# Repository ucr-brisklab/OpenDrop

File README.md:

## OpenDrop 

Open Source Digital Microfluidics Bio Lab

### Brisk-lab's v4.0 OpenDrop

### Open Source Digital Microfluidics Bio Lab

OpenDrop is a new design for an open source digital microfludics platform for research purposes. The device uses recent electro-wetting technology to control small droplets of liquids. Potential applications are lab on a chip devices for automating processes of digital biology. How ever the present design should also open the technology to other field and allow experimentation to find new applications. Including the field of art, music, games and education.

For more info on the open source project see:

http://www.gaudi.ch/OpenDrop

### License

OpenDrop, all design files and software are licensed under a GNU GENERAL PUBLIC LICENSE
See license file in the repository.

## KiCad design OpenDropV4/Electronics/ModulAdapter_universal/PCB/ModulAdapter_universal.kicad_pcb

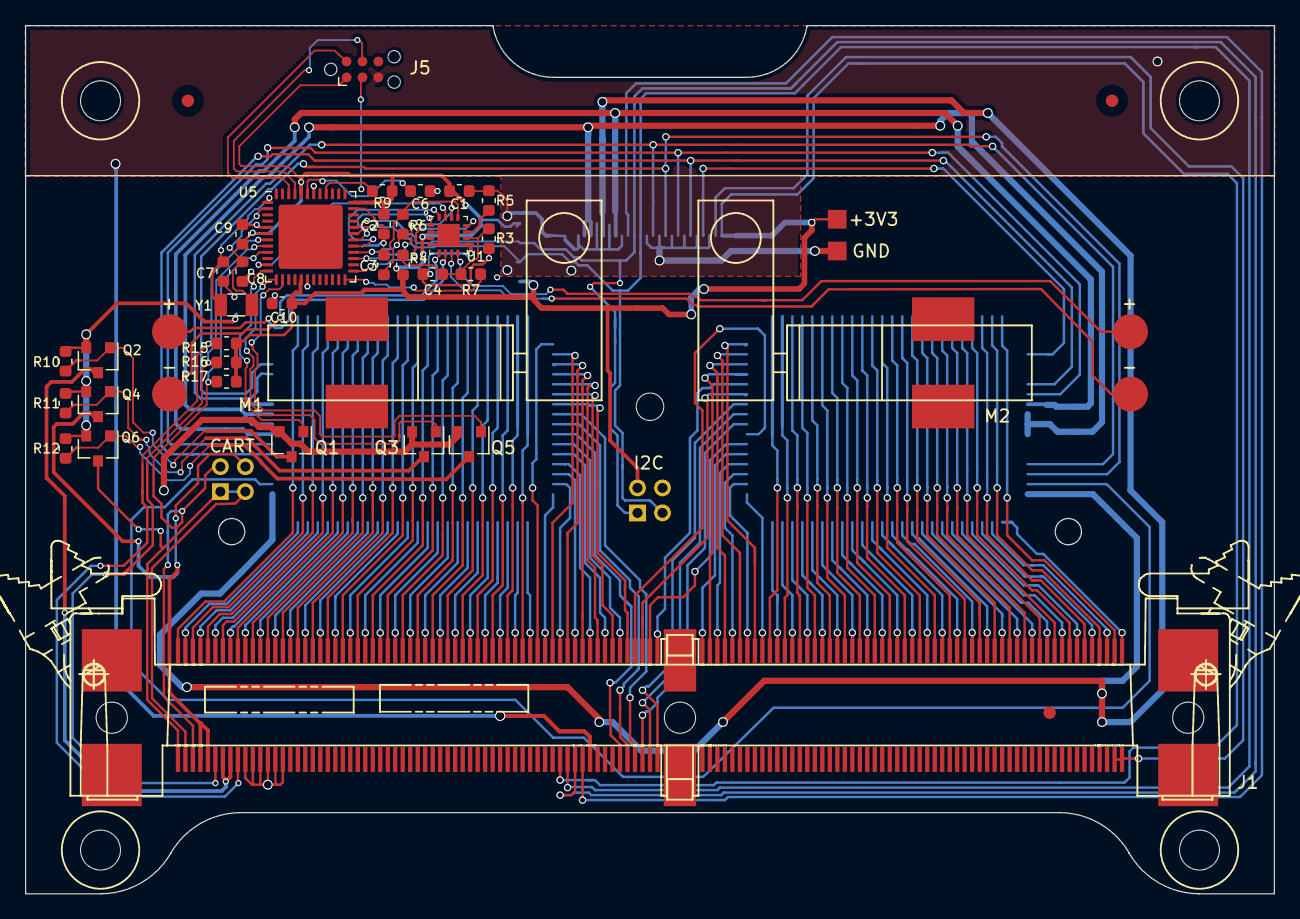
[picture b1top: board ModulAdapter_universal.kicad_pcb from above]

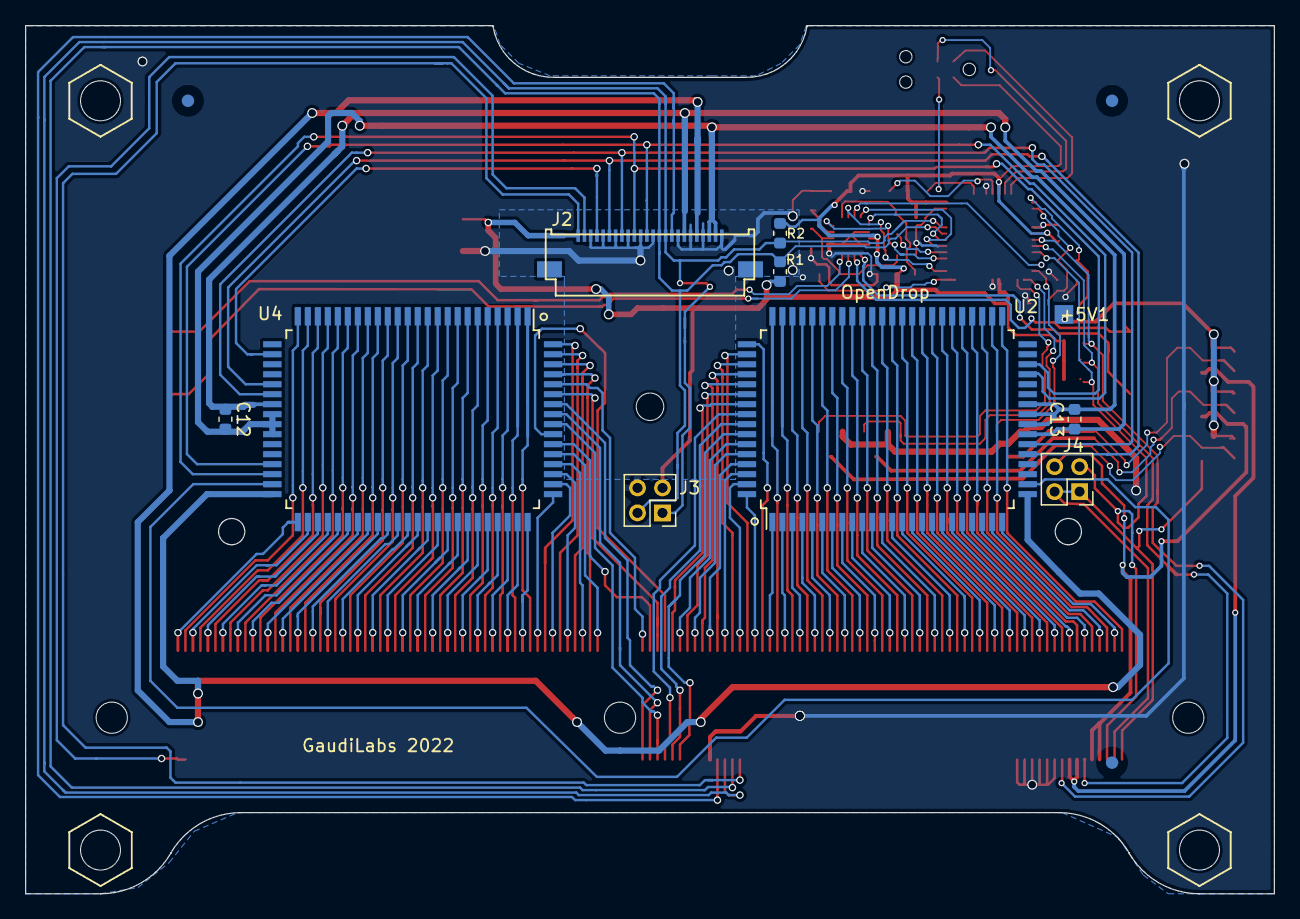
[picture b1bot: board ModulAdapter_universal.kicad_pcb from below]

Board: 2 copper layers, 100.0 x 69.5 mm, 56 parts (13 on the bottom side), 176 nets.

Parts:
+3V3, +5V1: ScrewPad2; Measurement_Point_Square-SMD-Pad_Small
C1, C4, C9, C10, C12, C13: 100nF; C_0603_1608Metric
C2: 10uF; C_0603_1608Metric
C3: 22nF; C_0603_1608Metric
C6: 1uF; C_0603_1608Metric
C7, C8: 22pF; C_0603_1608Metric
FID1, FID2, FID3, FID4, FID5, FID6: Fiducial; Fiducial_1mm_Dia_2.54mm_Outer_CopperBottom
GND1: ScrewPad2; Measurement_Point_Square-SMD-Pad_Small
H1, H2, H3, H4: MountingHole; MountingHoleM3
J1: Mini_Dimm_244; MiniDimm_06_244_200
J2: Conn_01x24_Female; FFC_MOLEX_EASYON_05mm_24
J3, J4: Conn_02x02_Top_Bottom; PinHeader_2x02_P2.00mm_Vertical
J5: Conn_02x03_Odd_Even; Tag-Connect_TC2030-IDC-NL_2x03_P1.27mm_Vertical
M1: Motor_DC; GreaMotor6mm_Magnet_l
M2: Motor_DC; GreaMotor6mm_Magnet
Q1, Q3, Q5: Q_NMOS_GSD; SOT-23
Q2, Q4, Q6: AO3401A; SOT-23
R1, R2, R9, R10, R11, R12, R15, R16, R17: 10k; R_0603_1608Metric
R3, R7: 4.7k; R_0603_1608Metric
R4: 100k; R_0603_1608Metric
R5: 47k; R_0603_1608Metric
R6: 4.7k (10k); R_0603_1608Metric
U1: TC78H660FTG; P-VQFN16-0303-0.50-001
U2, U4: HV507; PQFP-80_14x20mm_Pitch0.8mm
U5: SAMD21G18B; QFN-48-1EP_7x7mm_P0.5mm_EP5.15x5.15mm
Y1: 32 765; Crystal_SMD_3215-2Pin_3.2x1.5mm

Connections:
+3V3: +3V3.1, C1.1, C2.1, C9.1, C10.1, J1.52, J2.1, J3.3, J5.1, R1.1, R2.1, R4.1, R9.1, R15.1, R16.1, R17.1, U1.3, U5.6, U5.17, U5.36, U5.44
+5V: +5V1.1, Q2.2, Q4.2, Q6.2, R10.1, R11.1, R12.1
BL_C: J2.6, U2.29, U4.29
BOOST: R7.2, U5.24
CLK_C: J2.12, U2.37, U4.37
DIG0: J1.54, J2.15, J3.1, R2.2, U5.32
DIG1: J1.53, J2.14, J3.2, R1.2, U5.31
DI_C: J2.4, U4.26
ENABLE_A: U1.15, U5.11
ENABLE_B: U1.16, U5.29
GND: C1.2, C2.2, C3.2, C4.2, C6.2, C7.1, C8.1, C9.2, C10.2, GND1.1, J1.10, J1.11, J1.12, J1.13, J1.14, J1.15, J1.56, J2.3, J2.5, J2.7, J2.9, J2.11, J2.13, J2.17, J2.19, J2.21, J2.24, J3.4, J5.5, Q1.2, Q3.2, Q5.2, R3.2, R5.2, U1.2, U1.4, U1.9, U1.17, U5.5, U5.18, U5.35, U5.42
GND_C: C12.2, C13.2, J2.22, J2.23, U2.32, U2.33, U2.34, U4.32, U4.33, U4.34
H1: J1.7, J1.8, Q2.3
H3: J1.4, J1.5, J4.4, Q4.3
H5: J1.1, J1.2, J4.1, J4.2, Q6.3
HEATER1: Q1.1, U5.12
HEATER2: Q3.1, U5.13
HEATER3: Q5.1, U5.14
J3: J1.3, J4.3, R17.2, U5.9
LE_C: J2.10, U2.38, U4.38
MODE: R6.2, U5.28
unnamed: C3.1, R6.1, U1.13
unnamed: C4.1, R3.1, R4.2, R7.1, U1.10
unnamed: C6.1, U5.43
unnamed: C7.2, U5.1, Y1.1
unnamed: C8.2, U5.2, Y1.2
unnamed: J1.60, U2.74
unnamed: J1.61, U2.73
unnamed: J1.62, U2.72
unnamed: J1.63, U4.72
unnamed: J1.64, U4.73
unnamed: J1.65, U4.74
unnamed: J1.123, U2.41
unnamed: J1.124, U2.24
unnamed: J1.125, U2.42
unnamed: J1.126, U2.23
unnamed: J1.127, U2.43
unnamed: J1.128, U2.22
unnamed: J1.129, U2.44
unnamed: J1.130, U2.21
unnamed: J1.131, U2.45
unnamed: J1.132, U2.20
unnamed: J1.133, U2.46
unnamed: J1.134, U2.19
unnamed: J1.135, U2.47
unnamed: J1.136, U2.18
unnamed: J1.137, U2.48
unnamed: J1.138, U2.17
unnamed: J1.139, U2.49
unnamed: J1.140, U2.16
unnamed: J1.141, U2.50
unnamed: J1.142, U2.15
unnamed: J1.143, U2.51
unnamed: J1.144, U2.14
unnamed: J1.145, U2.52
unnamed: J1.146, U2.13
unnamed: J1.147, U2.53
unnamed: J1.148, U2.12
unnamed: J1.149, U2.54
unnamed: J1.150, U2.11
unnamed: J1.151, U2.55
unnamed: J1.152, U2.10
unnamed: J1.153, U2.56
unnamed: J1.154, U2.9
unnamed: J1.155, U2.57
unnamed: J1.156, U2.8
unnamed: J1.157, U2.58
unnamed: J1.158, U2.7
unnamed: J1.159, U2.59
unnamed: J1.160, U2.6
unnamed: J1.161, U2.60
unnamed: J1.162, U2.5
unnamed: J1.163, U2.61
unnamed: J1.164, U2.4
unnamed: J1.165, U2.62
unnamed: J1.166, U2.3
unnamed: J1.167, U2.63
unnamed: J1.168, U2.2
unnamed: J1.169, U2.64
unnamed: J1.170, U2.1
unnamed: J1.171, U2.65
unnamed: J1.172, U2.80
unnamed: J1.173, U2.66
unnamed: J1.174, U2.79
unnamed: J1.175, U2.67
unnamed: J1.176, U2.78
unnamed: J1.177, U2.68
unnamed: J1.178, U2.77
unnamed: J1.179, U2.69
unnamed: J1.180, U2.76
unnamed: J1.181, U2.70
unnamed: J1.182, U2.75
unnamed: J1.183, U2.71
unnamed: J1.184, U4.71
unnamed: J1.185, U4.75
unnamed: J1.186, U4.70
unnamed: J1.187, U4.76
unnamed: J1.188, U4.69
unnamed: J1.189, U4.77
unnamed: J1.190, U4.68
unnamed: J1.191, U4.78
unnamed: J1.192, U4.67
unnamed: J1.193, U4.79
unnamed: J1.194, U4.66
unnamed: J1.195, U4.80
unnamed: J1.196, U4.65
unnamed: J1.197, U4.1
unnamed: J1.198, U4.64
unnamed: J1.199, U4.2
unnamed: J1.200, U4.63
unnamed: J1.201, U4.3
unnamed: J1.202, U4.62
unnamed: J1.203, U4.4
unnamed: J1.204, U4.61
unnamed: J1.205, U4.5
unnamed: J1.206, U4.60
unnamed: J1.207, U4.6
unnamed: J1.208, U4.59
unnamed: J1.209, U4.7
unnamed: J1.210, U4.58
unnamed: J1.211, U4.8
unnamed: J1.212, U4.57
unnamed: J1.213, U4.9
unnamed: J1.214, U4.56
unnamed: J1.215, U4.10
unnamed: J1.216, U4.55
unnamed: J1.217, U4.11
unnamed: J1.218, U4.54
unnamed: J1.219, U4.12
unnamed: J1.220, U4.53
unnamed: J1.221, U4.13
unnamed: J1.222, U4.52
unnamed: J1.223, U4.14
unnamed: J1.224, U4.51
unnamed: J1.225, U4.15
unnamed: J1.226, U4.50
unnamed: J1.227, U4.16
unnamed: J1.228, U4.49
unnamed: J1.229, U4.17
unnamed: J1.230, U4.48
unnamed: J1.231, U4.18
unnamed: J1.232, U4.47
unnamed: J1.233, U4.19
unnamed: J1.234, U4.46
unnamed: J1.235, U4.20
unnamed: J1.236, U4.45
unnamed: J1.237, U4.21
unnamed: J1.238, U4.44
unnamed: J1.239, U4.22
unnamed: J1.240, U4.43
unnamed: J1.241, U4.23
unnamed: J1.242, U4.42
unnamed: J1.243, U4.24
unnamed: J1.244, U4.41
unnamed: M1.1, U1.5
unnamed: M1.2, U1.6
unnamed: M2.1, U1.8
unnamed: M2.2, U1.7
unnamed: Q1.3, Q2.1, R10.2
unnamed: Q3.3, Q4.1, R11.2
unnamed: Q5.3, Q6.1, R12.2
unnamed: R5.1, U1.11
unnamed: U2.26, U4.39
PHASE_A: U1.1, U5.30
PHASE_B: U1.14, U5.25
POL_C: J2.8, U2.30, U4.30
RESET: J5.3, R9.2, U5.40
SENS_PAD: J1.55, J2.16
STBY: U1.12, U5.27
SWCLK: J5.4, U5.45
SWDIO: J5.2, U5.46
TH1: J1.9, R15.2, U5.7
TH2: J1.6, R16.2, U5.8
VDD_C: C12.1, C13.1, J2.18, U2.31, U4.31
V_GND: J1.121, J1.122, J2.2
V_HV_C: J2.20, U2.25, U4.40

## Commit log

2022-07-05 getting our OpenDropv4 ready for refactor - removing deprecated (<v4) files
2022-07-06 getting magnet module 4.1 to work with our 4.0 opendrop
2022-07-06 soft i2c library added for controlling 4.1 magnet with 4.0 opendrop
2022-07-06 ready for refactor work
2022-07-10 timer library added with example use in .ino
2022-07-10 removed stash notes
2022-07-10 SM model finished, ISR setup, needs testing
2022-07-12 Deleted extraneous libraries accidentally added
2022-07-12 SM model running(?), ISR setup, needs testing (#4)
    * SM model finished, ISR setup, needs testing
    * Deleted extraneous libraries accidentally added
2022-07-13 interrupt-driven ticks not working as expected; will simply poll each clock tick
2022-07-17 Feedback control implemented, needs testing
2022-07-25 Dev (#5)
    * SM model finished, ISR setup, needs testing
    * Deleted extraneous libraries accidentally added
    * Feedback control implemented, needs testing
2022-08-02 test commit
2022-08-02 Menu possibly fixed from last push
2022-08-05 Menu possibly fixed (#6)
    * SM model finished, ISR setup, needs testing
    * Deleted extraneous libraries accidentally added
    * Feedback control implemented, needs testing
    * test commit
    * Menu possibly fixed from last push
2022-08-08 Feedback control adjusted, should no longer hang when feedback control is activated
2022-08-13 Feedback control should no longer hang (#7)
    * SM model finished, ISR setup, needs testing
    * Deleted extraneous libraries accidentally added
    * Feedback control implemented, needs testing
    * test commit
    * Menu possibly fixed from last push
    * Feedback control adjusted, should no longer hang when feedback control is activated
2022-08-13 Feedback control not being saved
2022-08-13 Feedback control should be saving now (#8)
    * SM model finished, ISR setup, needs testing
    * Deleted extraneous libraries accidentally added
    * Feedback control implemented, needs testing
    * test commit
    * Menu possibly fixed from last push
    * Feedback control adjusted, should no longer hang when feedback control is activated
2022-08-16 Breakout added to control loop, some more code added to loop
2022-08-16 Added breakout to control loop, added some more code in the hopes that it works (#9)
    * SM model finished, ISR setup, needs testing
    * Deleted extraneous libraries accidentally added
    * Feedback control implemented, needs testing
    * test commit
    * Menu possibly fixed from last push
    * Feedback control adjusted, should no longer hang when feedback control is activated
2022-08-16 Increments variable now
2022-08-16 Breakout variable now increments (#10)
    * SM model finished, ISR setup, needs testing
    * Deleted extraneous libraries accidentally added
    * Feedback control implemented, needs testing
    * test commit
    * Menu possibly fixed from last push
    * Feedback control adjusted, should no longer hang when feedback control is activated
